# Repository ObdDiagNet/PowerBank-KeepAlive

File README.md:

Power Bank Keep Alive
==========================================

<p>Power banks often shut down when connected to low current devices as they designed to provide a power while charging a smartphone and to cut it off when the current drops below the threshold. This project started when I wanted to power my smartphone acting as a tethering device when camping. Eventually, smartphone battery died but charging from power bank didn’t kick off. The smartphone and power bank were placed on top of nearest pine tree to provide a better reception and it was a challenge every time remove it and charge. The next time my friend got a smartphone with weak battery and powering it from power bank didn’t help either as it disconnected the exact moment when smartphone charging completed and not resumed charging when smartphone battery was low. I have figured out that simulating a load through periodic current draw, around 100 mA, shorter than the power bank’s shutdown interval, could prevent the power bank from powering turning off. The idea is not new, I have seen similar schematic posted on the Web in many places. The device is built around CMOS 555 timer to minimize the current draw by timer itself. The gate resistor for Q1 is not required as CMOS timer has a sufficient source resistance themselves. The frequency and duty cycle adjusted using trim potentiometers to set to minimum power consumption but keep the power bank alive. The LED allows you to see the device activity. Some power banks require about 100 mA load current to keep them alive but it could be less, 50 or even 15 mA. Actually, if your power bank needs only 15 mA you do not need this device, just connect 330 ohm resistor to make it happy. On contrary, some power banks seem to be checking for constant power consumption and simulating periodical loads not helping to trick them. My original idea was to keep the duty cycle fixed and adjust only frequency but unfortunately it didn’t work and schematic ended up with two trimmers.</p><p><b>Note: Printed circuit board layout is in Eagle 9 format.</b><p>
<p>&nbsp;</p>

<p>These blank PCBs are available from PCBWay: http://www.pcbway.com/project/shareproject/Keep_power_bank_alive_26bb6bb9.html</p>

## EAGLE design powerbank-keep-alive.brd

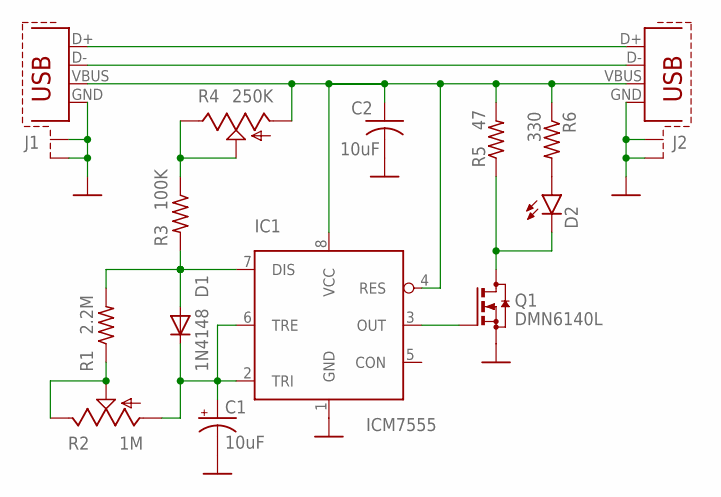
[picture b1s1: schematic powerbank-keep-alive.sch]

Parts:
C1: 10uF; CPOL_0805
C2: 10uF; C0805
D1: 1N4148; SOD123
D2: Red; CHIP-LED0805
IC1: ICM7555; SO-8
J1: USB-SHIELD-A-H; USB-A-H
J2: USB-SHIELD-FEMALE; USB-A-FEMALE
Q1: DMN6140L; SOT23
R1: 2.2M; R0805
R2: 1M; B25P
R3: 100K; R0805
R4: 250K; B25P
R5: 47; R2010
R6: 330; R0805

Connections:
GND: C1.-, C2.2, IC1.1 (GND), J1.GND, J1.GND2 (S1), J1.GND3 (S2), J2.GND, J2.S1, J2.S2, Q1.2 (S)
unnamed: C1.+, D1.C, IC1.2 (TRI), IC1.6 (TRE), R2.A
unnamed: IC1.3 (OUT), Q1.1 (G)
unnamed: D2.C, Q1.3 (D), R5.1
unnamed: D2.A, R6.2
unnamed: D1.A, IC1.7 (DIS), R1.2, R3.2
unnamed: R3.1, R4.E, R4.S
unnamed: R1.1, R2.E, R2.S
unnamed: J1.D-, J2.D-
unnamed: J1.D+, J2.D+
PWR: C2.1, IC1.4 (RES), IC1.8 (VCC), J1.VBUS, J2.VBUS, R4.A, R5.2, R6.1

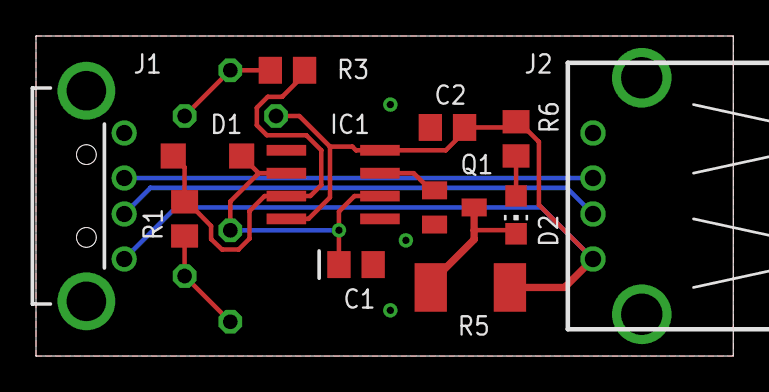
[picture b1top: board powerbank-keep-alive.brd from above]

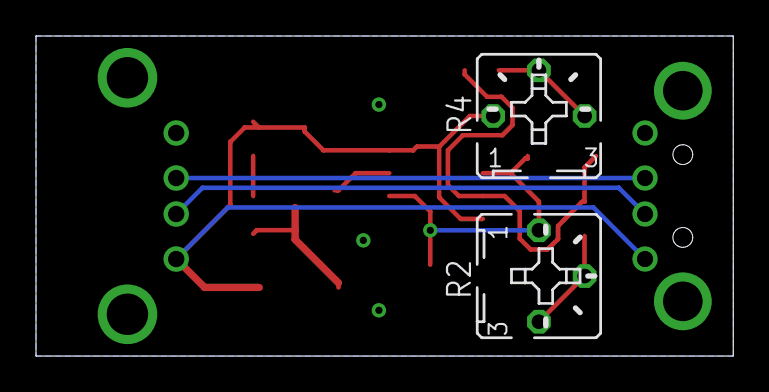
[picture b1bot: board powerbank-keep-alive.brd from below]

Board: 2 copper layers, 38.7 x 17.8 mm, 14 parts (2 on the bottom side), 11 nets.

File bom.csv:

Parts,Value,Package,Description,Note
J1,,USB-A-H,USB type a plug right angle t/h,
J2,,USB-A-FEMALE,USB type A receptacle right angle t/h,
C1,10uF 10V,0805,Tantalum SMD capacitor,
C2,10uF 10V,0805,Ceramic SMD capacitor,
R1,2.2M,0805,SMD resistor,
R2,1M,3306P,Bourns 3306P-1-254,
R3,100K,0805,SMD resistor,
R4,250K,B25P,Bourns 3306P-1-254,
R5,47,R2010,SMD resistor,
R6,330,0805,SMD resistor,
D1,1N4148,SOD123,SMD diode,
D2,Red,0805,SMD LED,
Q1,DMN6140L,SOT23,DMN6140L-13,Could be TLC555 or other CMOS 555 timers
IC1,ICM7555,SO-8,CMOS 555 timer,"Could be PMV450ENEA, NDS7002A"

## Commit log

2024-09-30 Initial release
2024-09-30 Added project files
2024-09-30 Tantalum capacitor value
2024-09-30 Readme
2024-09-30 Testing
2024-09-30 More description
2024-10-01 Version 2 image
2024-10-01 Added BOM
2024-10-01 More info
